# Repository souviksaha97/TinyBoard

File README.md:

# TinyBoard v1.0

A basic development board based on the 8-bit AVR microcontroller ATTiny85. This is my first development board.

Last modified - 05102019

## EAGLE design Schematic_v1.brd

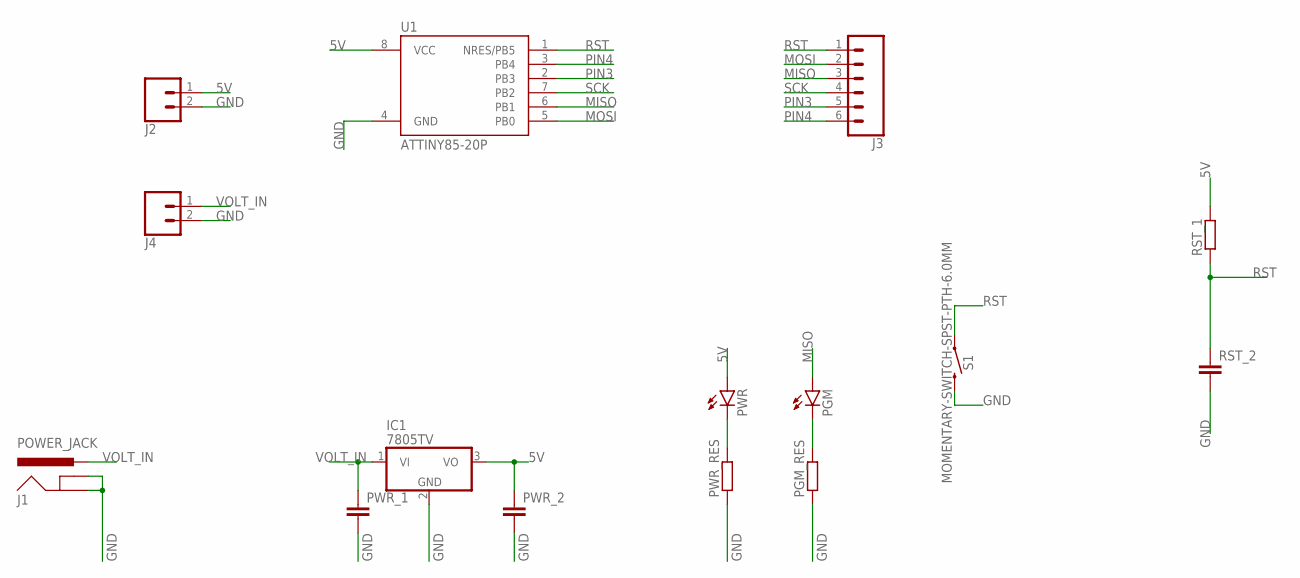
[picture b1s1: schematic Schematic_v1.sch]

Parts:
IC1: 7805TV; TO220V
J1: POWER_JACK; POWER_JACK_PTH
J2, J4: CONN_021X02_NO_SILK; 1X02_NO_SILK
J3: CONN_06NO_SILK_NO_POP; 1X06_NO_SILK
PGM: LED3MM
PGM_RES: R-EU_0207/2V; 0207/2V
PWR: LED3MM
PWR_1, PWR_2: C-EU025-025X050; C025-025X050
PWR_RES: R-EU_0207/2V; 0207/2V
RST_1: R-EU_0207/2V; 0207/2V
RST_2: C-EU025-025X050; C025-025X050
S1: MOMENTARY-SWITCH-SPST-PTH-6.0MM; TACTILE_SWITCH_PTH_6.0MM
U1: ATTINY85-20P; PDIP08_300MIL

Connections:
5V: IC1.3 (VO), J2.1, PWR.A, PWR_2.1, RST_1.2, U1.8 (VCC)
GND: IC1.2 (GND), J1.GND, J1.GNDBREAK, J2.2, J4.2, PGM_RES.1, PWR_1.2, PWR_2.2, PWR_RES.1, RST_2.2, S1.3 (2), U1.4 (GND)
MISO: J3.3, PGM.A, U1.6 (PB1)
MOSI: J3.2, U1.5 (PB0)
unnamed: PWR.K (C), PWR_RES.2
unnamed: PGM.K (C), PGM_RES.2
PIN3: J3.5, U1.2 (PB3)
PIN4: J3.6, U1.3 (PB4)
RST: J3.1, RST_1.1, RST_2.1, S1.1, U1.1 (NRES/PB5)
SCK: J3.4, U1.7 (PB2)
VOLT_IN: IC1.1 (VI), J1.PWR, J4.1, PWR_1.1

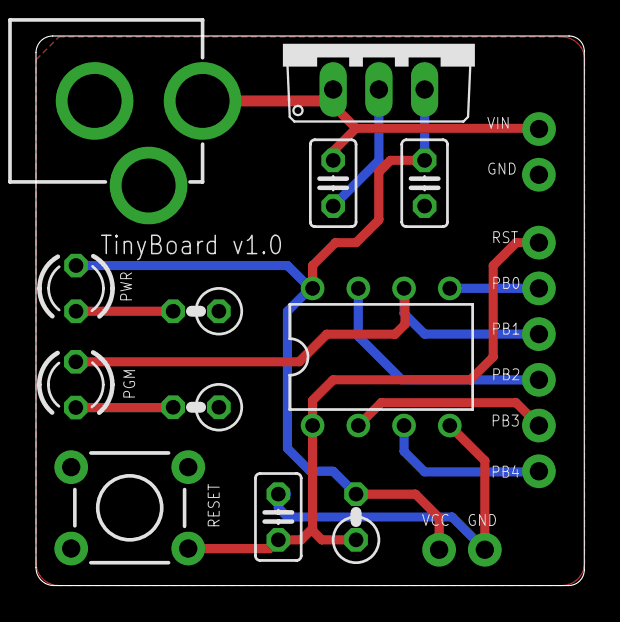
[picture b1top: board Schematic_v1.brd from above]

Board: 2 copper layers, 30.5 x 30.5 mm, 15 parts (0 on the bottom side), 11 nets.

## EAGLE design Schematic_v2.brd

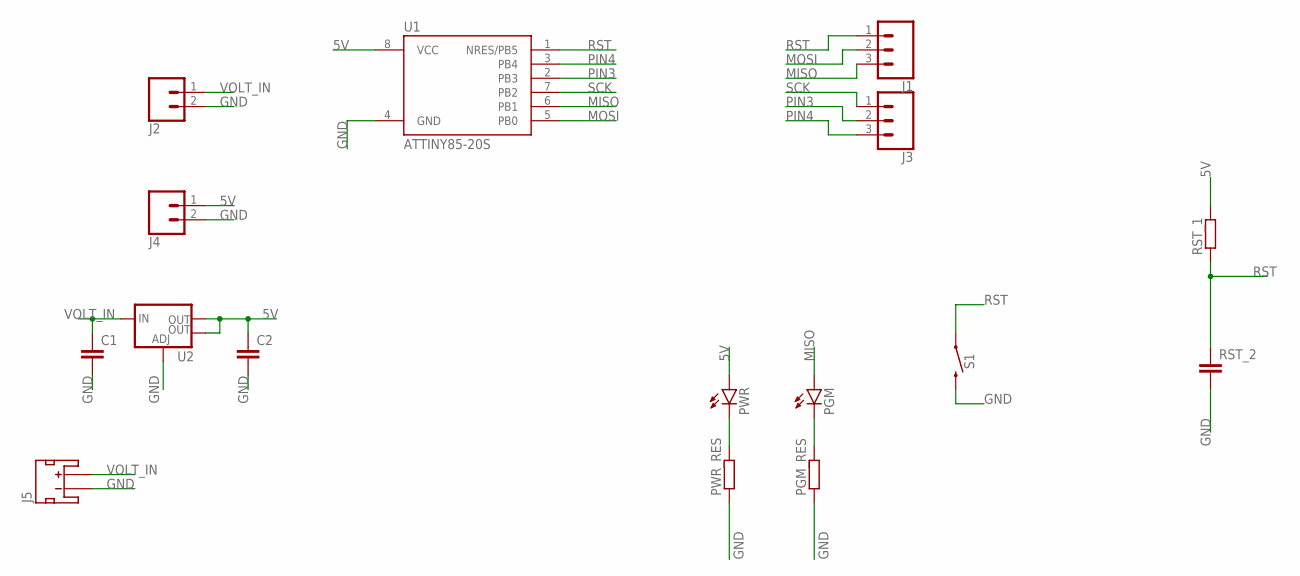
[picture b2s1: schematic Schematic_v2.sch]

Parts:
C1, C2: C-EUC0805; C0805
J1, J3: CONN_031X03_NO_SILK; 1X03_NO_SILK
J2, J4: CONN_021X02_NO_SILK; 1X02_NO_SILK
J5: JST_2MM_MALE; JST-2-SMD
PGM: LEDSML0805; SML0805
PGM_RES: R-EU_R0805; R0805
PWR: LEDSML0805; SML0805
PWR_RES: R-EU_R0805; R0805
RST_1: R-EU_R0805; R0805
RST_2: C-EUC0805; C0805
S1: MOMENTARY-SWITCH-SPST-SMD-6.0X3.5MM; TACTILE_SWITCH_SMD_6.0X3.5MM
U1: ATTINY85-20S; SOIC8_EIAJ_208MIL
U2: V_REG_LM1117SOT223; SOT223

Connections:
5V: C2.1, J4.1, PWR.A, RST_1.2, U1.8 (VCC), U2.2 (OUT), U2.4 (OUT)
GND: C1.2, C2.2, J2.2, J4.2, J5.1 (-), PGM_RES.1, PWR_RES.1, RST_2.2, S1.2, U1.4 (GND), U2.1 (ADJ)
MISO: J1.3, PGM.A, U1.6 (PB1)
MOSI: J1.2, U1.5 (PB0)
unnamed: PWR.C, PWR_RES.2
unnamed: PGM.C, PGM_RES.2
PIN3: J3.2, U1.2 (PB3)
PIN4: J3.3, U1.3 (PB4)
RST: J1.1, RST_1.1, RST_2.1, S1.1, U1.1 (NRES/PB5)
SCK: J3.1, U1.7 (PB2)
VOLT_IN: C1.1, J2.1, J5.2 (+), U2.3 (IN)

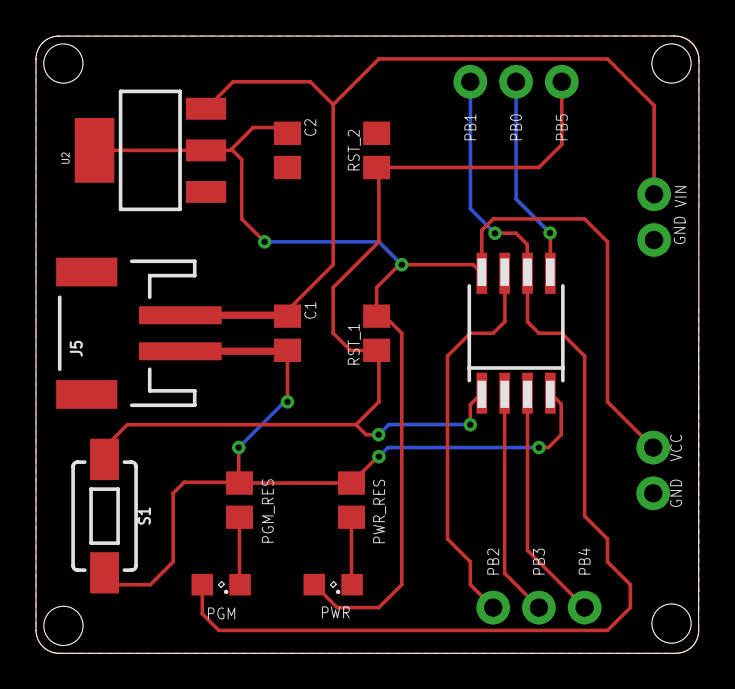
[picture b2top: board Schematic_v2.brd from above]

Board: 2 copper layers, 36.8 x 34.3 mm, 16 parts (0 on the bottom side), 11 nets.

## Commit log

2019-10-20 First version
2019-10-20 Added images to the project
2019-10-26 Set theme jekyll-theme-cayman

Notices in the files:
parts and their libraries:
SparkFun-Connectors: Licensing: Creative Commons ShareAlike 4.0 International - https://creativecommons.org/licenses/by-sa/4.0
